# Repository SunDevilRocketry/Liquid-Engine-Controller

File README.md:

<h1>Liquids Engine Controller</h1>

<p>Current PCB Revision: 5.1</p>
<p>PCB Part Number: L0002</p>

<p>The Liquid Engine Controller is the main embedded processor of Sun Devil Rocketry's Liquid Engine. As the brains of the engine, the controller is responsible for executing propellant feed sequences semi-autonomously, logging sensor data, and transmitting engine telemetry. The controller is equipped with an STM32 ARM Cortex M7 processor and 4Mb of external flash for data logging. The board includes a micro-SD card jack for easy access to the logged data. The board includes many power sources for flexible use of the controller during testing and normal operation. These include a 12V power jack, a USB Type B connector, and a 2-pin male pin header. The board includes short circuit protection on the main power rail and regulates the multiplexed supply to 5V and 3.3V with a buck converter and linear regulator (LDO) respectively. The board interfaces with a PC through either the USB port or the 8-pin telemetry connector, which allows wireless transceiver modules with either a UART or SPI interface to be connected. The screw terminals on the board connect to the ignition circuitry. An e-match is used to initiate combustion, and two continuity wires are used to provide the controller feedback on the ignition state. The ignition current is routed through an additional screw terminal which serves as a safety/arming switch. The board interfaces with all of the engine sensors, including eight pressure transducers, a thermocouple, and a load cell. The pressure transducer outputs are amplified with a programmable-gain instrumentation amplifier, which allows for up to 256 calibration settings. The thermocouple output is processed using a cold-junction compensation IC. Additionally, the board includes a reset button and several LEDs for visual indication of power and firmware status.
</p>

<p><b>Working Directory Structure:</b></p>

<p>
   cad: 3d models

   doc: documentation

   img: images of circuit/footprints for github display 
   
   lib: libraries for schematic symbols and footprints

   production: files needed for pcb fabrication, e.g. gerbers, profile, drill file

   sim: simulation models/files 

   src: source design files, e.g. schematic and PCB layout files
</p>

<h2>3D Model: </h2>

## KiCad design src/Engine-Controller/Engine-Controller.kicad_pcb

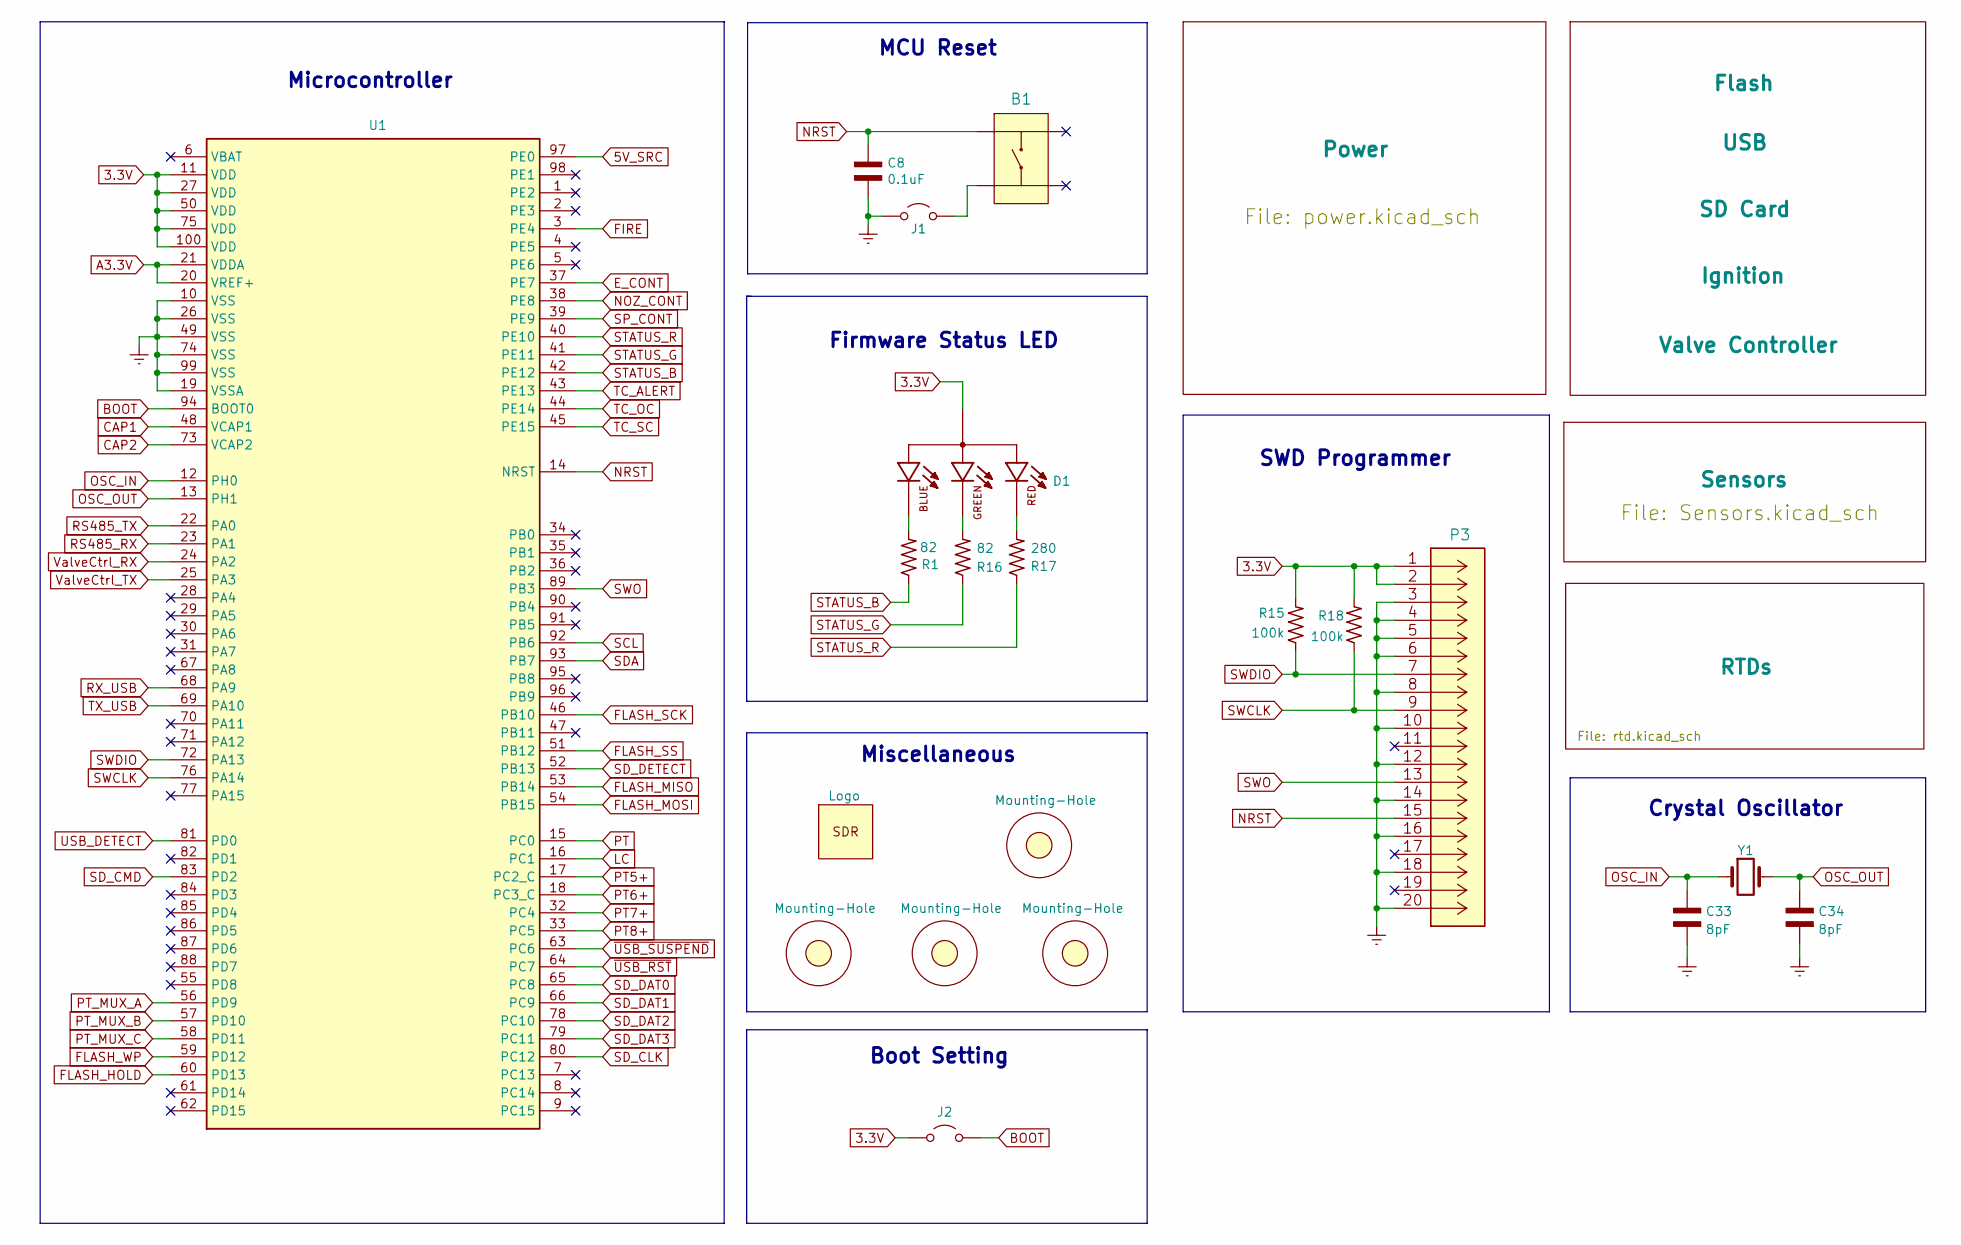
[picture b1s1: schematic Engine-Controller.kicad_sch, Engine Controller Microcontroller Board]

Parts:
B1: PTS647SM38SMTR2LFS
C8: 0.1uF; CAP_0603
C33, C34: 8pF; CAP_0603
D1: CLMVC-FKA-CL1D1L71BB7C3C3
H1, H4, H5, H6: Mounting-Hole; MountingHole_4.3mm_M4_DIN965
J1, J2: Jumper_NO; Jumper-NO
LOGO2: Logo
P3: 3220-20-0200-00
R1, R16: 82; RES_0603
R15, R18: 100k; RES_0603
R17: 280; RES_0603
U1: STM32H750VBTx; STM32H750VBT6
Y1: ECS-240-18-33-JGN-TR

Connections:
3.3V: D1.1, J2.1 (A), P3.1, P3.2, R15.2, R18.2, U1.11 (VDD), U1.27 (VDD), U1.50 (VDD), U1.75 (VDD), U1.100 (VDD); also elsewhere on the board
5V_SRC: U1.97 (PE0); also elsewhere on the board
A3.3V: U1.20 (VREF+), U1.21 (VDDA); also elsewhere on the board
BOOT: J2.2 (B), U1.94 (BOOT0)
CAP1: U1.48 (VCAP1); also elsewhere on the board
CAP2: U1.73 (VCAP2); also elsewhere on the board
E_CONT: U1.37 (PE7); also elsewhere on the board
Earth: C8.1, C33.2, C34.2, J1.1 (A), P3.3, P3.4, P3.5, P3.6, P3.8, P3.10, P3.12, P3.14, P3.16, P3.18, P3.20, U1.10 (VSS), U1.19 (VSSA), U1.26 (VSS), U1.49 (VSS), U1.74 (VSS), U1.99 (VSS); also elsewhere on the board
FIRE: U1.3 (PE4); also elsewhere on the board
FLASH_HOLD: U1.60 (PD13); also elsewhere on the board
FLASH_MISO: U1.53 (PB14); also elsewhere on the board
FLASH_MOSI: U1.54 (PB15); also elsewhere on the board
FLASH_SCK: U1.46 (PB10); also elsewhere on the board
FLASH_SS: U1.51 (PB12); also elsewhere on the board
FLASH_WP: U1.59 (PD12); also elsewhere on the board
LC: U1.16 (PC1); also elsewhere on the board
NOZ_CONT: U1.38 (PE8); also elsewhere on the board
NRST: B1.3, C8.2, P3.15, U1.14 (NRST)
unnamed: D1.2, R1.2
unnamed: D1.3, R16.2
unnamed: D1.4, R17.2
unnamed: B1.1, J1.2 (B)
OSC_IN: C33.1, U1.12 (PH0), Y1.1
OSC_OUT: C34.1, U1.13 (PH1), Y1.3
PT: U1.15 (PC0); also elsewhere on the board
PT5+: U1.17 (PC2_C); also elsewhere on the board
PT6+: U1.18 (PC3_C); also elsewhere on the board
PT7+: U1.32 (PC4); also elsewhere on the board
PT8+: U1.33 (PC5); also elsewhere on the board
PT_MUX_A: U1.56 (PD9); also elsewhere on the board
PT_MUX_B: U1.57 (PD10); also elsewhere on the board
PT_MUX_C: U1.58 (PD11); also elsewhere on the board
RS485_RX: U1.23 (PA1); also elsewhere on the board
RS485_TX: U1.22 (PA0); also elsewhere on the board
RX_USB: U1.68 (PA9); also elsewhere on the board
SCL: U1.92 (PB6); also elsewhere on the board
SDA: U1.93 (PB7); also elsewhere on the board
SD_CLK: U1.80 (PC12); also elsewhere on the board
SD_CMD: U1.83 (PD2); also elsewhere on the board
SD_DAT0: U1.65 (PC8); also elsewhere on the board
SD_DAT1: U1.66 (PC9); also elsewhere on the board
SD_DAT2: U1.78 (PC10); also elsewhere on the board
SD_DAT3: U1.79 (PC11); also elsewhere on the board
SD_DETECT: U1.52 (PB13); also elsewhere on the board
SP_CONT: U1.39 (PE9); also elsewhere on the board
STATUS_B: R1.1, U1.42 (PE12)
STATUS_G: R16.1, U1.41 (PE11)
STATUS_R: R17.1, U1.40 (PE10)
SWCLK: P3.9, R18.1, U1.76 (PA14)
SWDIO: P3.7, R15.1, U1.72 (PA13)
SWO: P3.13, U1.89 (PB3)
TC_ALERT: U1.43 (PE13); also elsewhere on the board
TC_OC: U1.44 (PE14); also elsewhere on the board
TC_SC: U1.45 (PE15); also elsewhere on the board
TX_USB: U1.69 (PA10); also elsewhere on the board
USB_DETECT: U1.81 (PD0); also elsewhere on the board
ValveCtrl_RX: U1.24 (PA2); also elsewhere on the board
ValveCtrl_TX: U1.25 (PA3); also elsewhere on the board
~USB_RST: U1.64 (PC7); also elsewhere on the board
~USB_SUSPEND: U1.63 (PC6); also elsewhere on the board

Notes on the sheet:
SWD Programmer
Miscellaneous
Crystal Oscillator
Microcontroller
Boot Setting
Firmware Status LED
MCU Reset

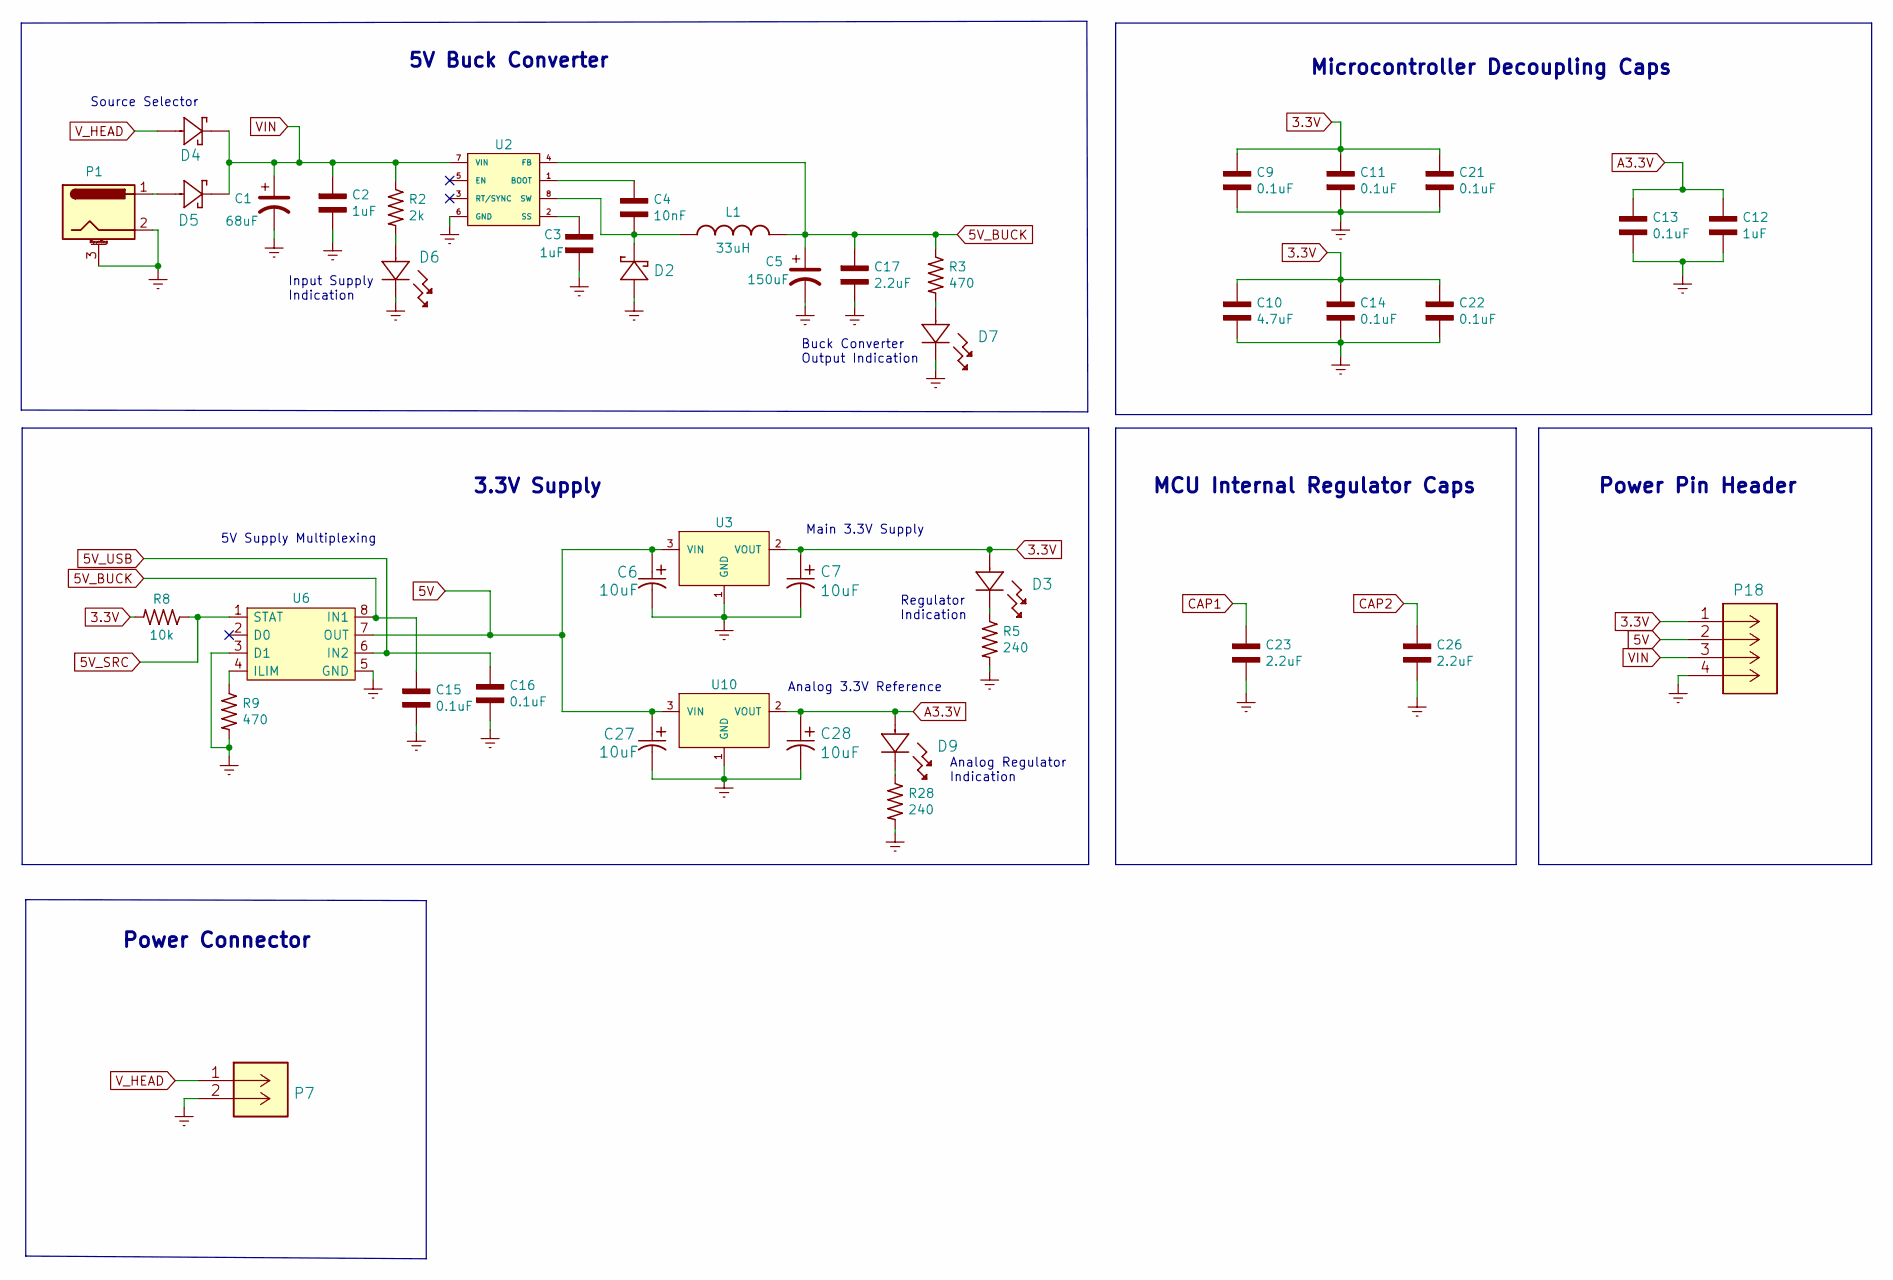
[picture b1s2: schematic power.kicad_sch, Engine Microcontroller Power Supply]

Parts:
C1: 68uF; EEEFPV680XAP
C2, C3, C12: 1uF; CAP_0603
C4: 10nF; CAP_0603
C5: 150uF; EEEFP1E151AL
C6, C7, C27, C28: 10uF; T491A106K010AT
C9, C11, C13, C14, C15, C16, C21, C22: 0.1uF; CAP_0603
C10: 4.7uF; CAP_0603
C17, C23, C26: 2.2uF; CAP_0603
D2: RB160VAM-60TR
D3, D6, D7, D9: SML-LX1206GC-TR
D4, D5: SM5819PL-TP
L1: 33uH; SRP1038A-330M
P1: EJ508A; 12V_power_jack
P7: 647676-2
P18: PPTC041LFBN-RC
R2: 2k; RES_0603
R3, R9: 470; RES_0603
R5, R28: 240; RES_0603
R8: 10k; RES_0603
U2: LM22672MRE-5.0_NOPB
U3, U10: LMS8117AMP-3.3_NOPB; LMS8117AMP-3.3NOPB
U6: TPS2115APWR

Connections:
3.3V: C7.1, C9.2, C10.2, C11.2, C14.2, C21.2, C22.2, D3.2, P18.1 (+12V), R8.2, U3.2 (VOUT); also elsewhere on the board
5V: C6.1, C27.1, P18.2 (GND), U3.3 (VIN), U6.7 (OUT), U10.3 (VIN); also elsewhere on the board
5V_BUCK: C5.1, C15.2, C17.2, L1.2, R3.1, U2.4 (FB), U6.8 (IN1)
5V_SRC: R8.1, U6.1 (STAT); also elsewhere on the board
5V_USB: C16.2, U6.6 (IN2); also elsewhere on the board
A3.3V: C12.2, C13.2, C28.1, D9.2, U10.2 (VOUT); also elsewhere on the board
CAP1: C23.2; also elsewhere on the board
CAP2: C26.2; also elsewhere on the board
Earth: C1.2, C2.1, C3.1, C5.2, C6.2, C7.2, C9.1, C10.1, C11.1, C12.1, C13.1, C14.1, C15.1, C16.1, C17.1, C21.1, C22.1, C23.1, C26.1, C27.2, C28.2, D2.2, D6.1, D7.1, P1.2, P1.3 (MountPin), P7.2, P18.4, R5.2, R9.2, R28.2, U2.6 (GND), U3.1 (GND), U6.3 (D1), U6.5 (GND), U10.1 (GND); also elsewhere on the board
unnamed: D3.1, R5.1
unnamed: D5.2, P1.1
unnamed: D6.2, R2.2
unnamed: D7.2, R3.2
unnamed: D9.1, R28.1
unnamed: C4.2, U2.1 (BOOT)
unnamed: C3.2, U2.2 (SS)
unnamed: C4.1, D2.1, L1.1, U2.8 (SW)
unnamed: R9.1, U6.4 (ILIM)
VIN: C1.1, C2.2, D4.1, D5.1, P18.3, R2.1, U2.7 (VIN); also elsewhere on the board
V_HEAD: D4.2, P7.1

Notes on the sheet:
Power Connector
Power Pin Header
5V Buck Converter
5V Supply Multiplexing
Main 3.3V Supply
Analog Regulator Indication
Regulator Indication
Buck Converter Output Indication
Microcontroller Decoupling Caps
Input Supply Indication
Analog 3.3V Reference
3.3V Supply
Source Selector
MCU Internal Regulator Caps

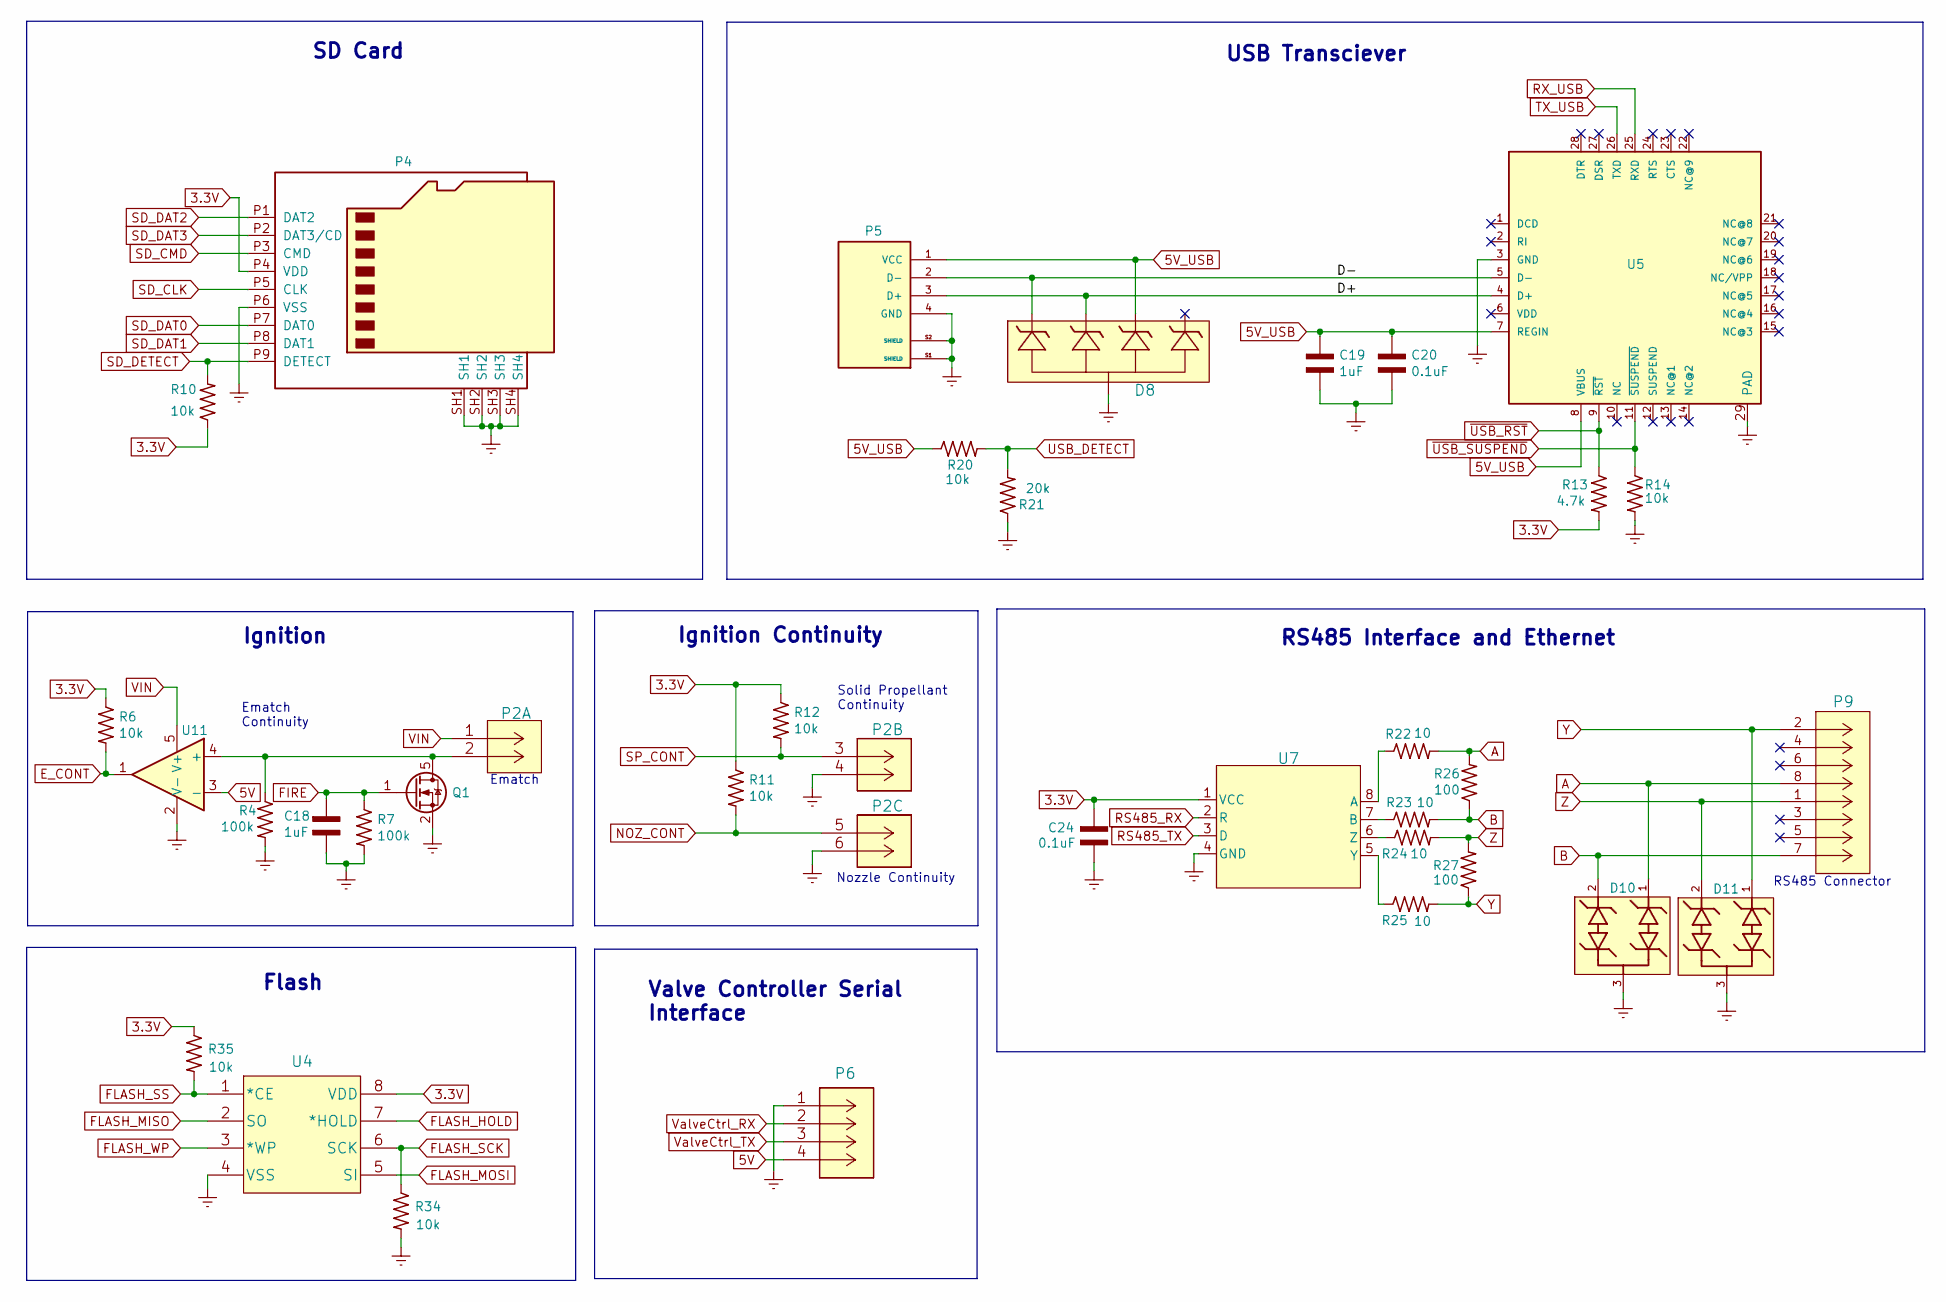
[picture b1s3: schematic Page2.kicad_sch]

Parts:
C18, C19: 1uF; CAP_0603
C20, C24: 0.1uF; CAP_0603
D8: SP0504BAHTG
D10, D11: SMBJ36CA-13-F; CDSOT23-SM712; PARTREV 20-2
P2: 282837-6
P4: Micro_SD_Card; MEM2075-00-140-01-A
P5: USB; USB-TypeB
P6: 140-504-415-000
P9: 54602-908LF
Q1: QS5U17TR
R4, R7: 100k; RES_0603
R6, R10, R11, R12, R14, R20, R34, R35: 10k; RES_0603
R13: 4.7k; RES_0603
R21: 20k; RES_0603
R22, R23, R24, R25: 10; RES_0603
R26, R27: 100; RES_0603
U4: SST25VF040B-50-4I-S2AE-T
U5: CP2102-GMR(QFN28); CP2012-GMR; MPN CP2102-GMR
U7: SN65HVD71DR
U11: TS391IYLT

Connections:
3.3V: C24.2, P4.P4 (VDD), R6.1, R10.1, R11.1, R12.1, R13.2, R35.1, U4.8 (VDD), U7.1 (VCC); also elsewhere on the board
5V: P6.4, U11.3 (-); also elsewhere on the board
5V_USB: C19.2, C20.2, D8.4, P5.1 (VCC), R20.1, U5.7 (REGIN), U5.8 (VBUS); also elsewhere on the board
/Page2/D+: D8.3, P5.3 (D+), U5.4 (D+)
/Page2/D-: D8.1, P5.2 (D-), U5.5 (D-)
A: D10.1, P9.8, R22.2, R26.2
B: D10.2, P9.7, R23.2, R26.1
E_CONT: R6.2, U11.1; also elsewhere on the board
Earth: C18.1, C19.1, C20.1, C24.1, D8.2, D10.3, D11.3, P2.4 (6), P2.6, P4.P6 (VSS), P4.SH1, P4.SH2, P4.SH3, P4.SH4, P5.4 (GND), P5.S1 (SHIELD), P5.S2 (SHIELD), P6.1 (+12V), Q1.2 (S), R4.2, R7.2, R14.2, R21.1, R34.2, U4.4 (VSS), U5.3 (GND), U5.29 (PAD), U7.4 (GND), U11.2 (V-); also elsewhere on the board
FIRE: C18.2, Q1.1 (G), R7.1; also elsewhere on the board
FLASH_HOLD: U4.7 (*HOLD); also elsewhere on the board
FLASH_MISO: U4.2 (SO); also elsewhere on the board
FLASH_MOSI: U4.5 (SI); also elsewhere on the board
FLASH_SCK: R34.1, U4.6 (SCK); also elsewhere on the board
FLASH_SS: R35.2, U4.1 (*CE); also elsewhere on the board
FLASH_WP: U4.3 (*WP); also elsewhere on the board
NOZ_CONT: P2.5, R11.2; also elsewhere on the board
unnamed: P2.2 (6), Q1.5 (D), R4.1, U11.4 (+)
unnamed: R22.1, U7.8 (A)
unnamed: R23.1, U7.7 (B)
unnamed: R25.1, U7.5 (Y)
unnamed: R24.1, U7.6 (Z)
RS485_RX: U7.2 (R); also elsewhere on the board
RS485_TX: U7.3 (D); also elsewhere on the board
RX_USB: U5.25 (RXD); also elsewhere on the board
SD_CLK: P4.P5 (CLK); also elsewhere on the board
SD_CMD: P4.P3 (CMD); also elsewhere on the board
SD_DAT0: P4.P7 (DAT0); also elsewhere on the board
SD_DAT1: P4.P8 (DAT1); also elsewhere on the board
SD_DAT2: P4.P1 (DAT2); also elsewhere on the board
SD_DAT3: P4.P2 (DAT3/CD); also elsewhere on the board
SD_DETECT: P4.P9 (DETECT), R10.2; also elsewhere on the board
SP_CONT: P2.3 (5), R12.2; also elsewhere on the board
TX_USB: U5.26 (TXD); also elsewhere on the board
USB_DETECT: R20.2, R21.2; also elsewhere on the board
VIN: P2.1 (5), U11.5 (V+); also elsewhere on the board
ValveCtrl_RX: P6.2 (GND); also elsewhere on the board
ValveCtrl_TX: P6.3; also elsewhere on the board
Y: D11.1, P9.2, R25.2, R27.1
Z: D11.2, P9.1, R24.2, R27.2
~USB_RST: R13.1, U5.9 (~RST); also elsewhere on the board
~USB_SUSPEND: R14.1, U5.11 (~SUSPEND); also elsewhere on the board

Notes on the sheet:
SD Card
RS485 Connector
Ematch
RS485 Interface and Ethernet
USB Transciever
Ignition Continuity
Ematch Continuity
Ignition
Flash
Nozzle Continuity
Solid Propellant Continuity
Valve Controller Serial Interface

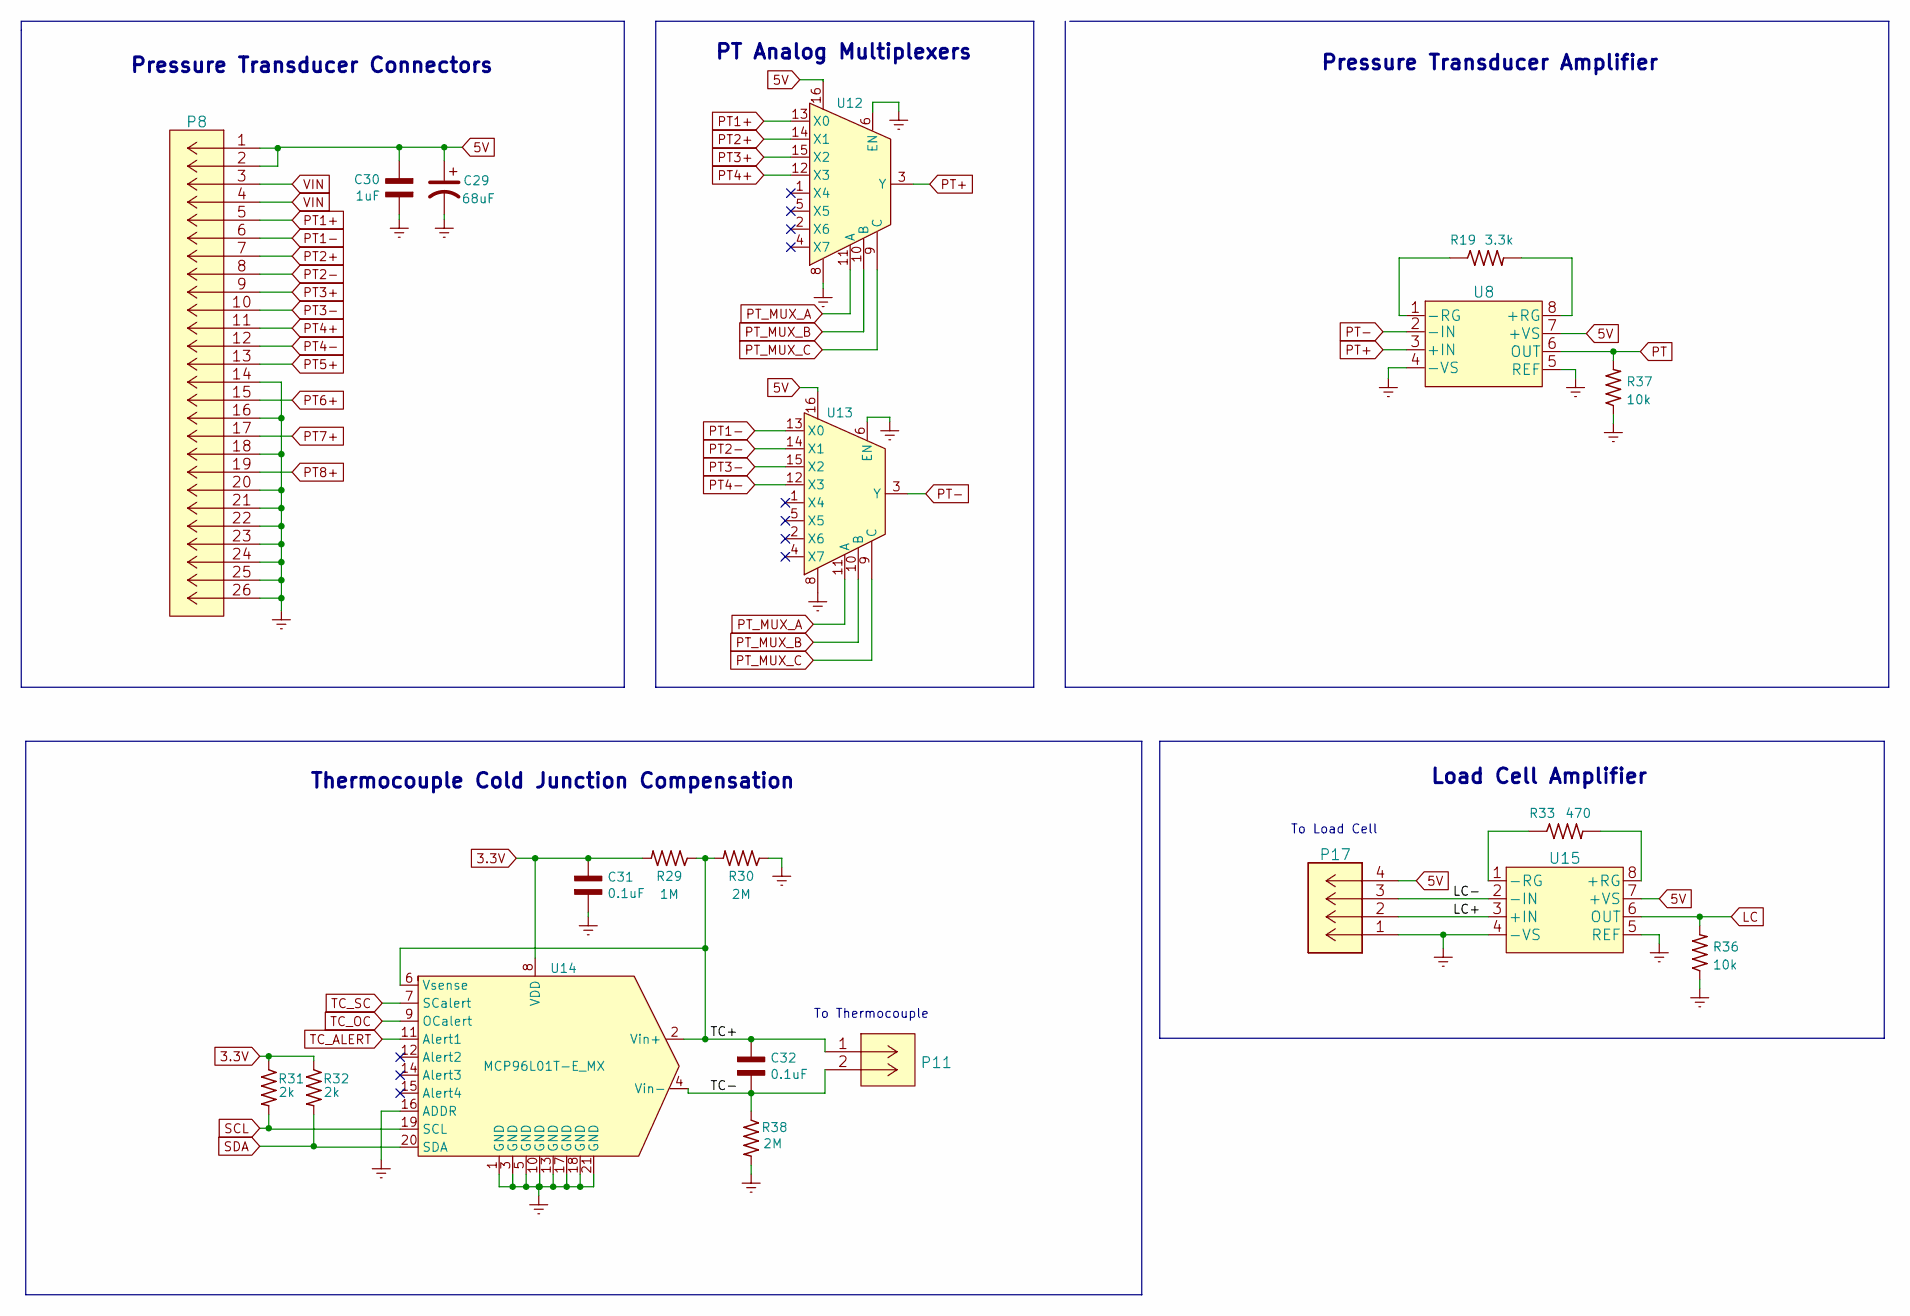
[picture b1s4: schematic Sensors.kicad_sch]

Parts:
C29: 68uF; EEEFPV680XAP
C30: 1uF; CAP_0603
C31, C32: 0.1uF; CAP_0603
P8: 20021511-00026T4LF
P11: 282837-2
P17: 0530470410
R19: 3.3k; RES_0805
R29: 1M; RES_0603
R30, R38: 2M; RES_0603
R31, R32: 2k; RES_0603
R33: 470; RES_0805
R36, R37: 10k; RES_0603
U8, U15: AD623ARZ-R7
U12, U13: MAX4617EUE+T; max4617eue
U14: MCP96L01T-E_MX

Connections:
3.3V: C31.2, R29.2, R31.1, R32.1, U14.8 (VDD); also elsewhere on the board
5V: C29.1, C30.2, P8.1, P8.2, P17.4, U8.7 (+VS), U12.16, U13.16, U15.7 (+VS); also elsewhere on the board
/Sensors/LC+: P17.2 (GND), U15.3 (+IN)
/Sensors/LC-: P17.3, U15.2 (-IN)
/Sensors/TC+: C32.2, P11.1 (5), R29.1, R30.2, U14.2 (Vin+), U14.6 (Vsense)
/Sensors/TC-: C32.1, P11.2 (6), R38.1, U14.4 (Vin-)
Earth: C29.2, C30.1, C31.1, P8.14, P8.16, P8.18, P8.20, P8.21, P8.22, P8.23, P8.24, P8.25, P8.26, P17.1 (+12V), R30.1, R36.1, R37.1, R38.2, U8.4 (-VS), U8.5 (REF), U12.6 (EN), U12.8, U13.6 (EN), U13.8, U14.1 (GND), U14.3 (GND), U14.5 (GND), U14.10 (GND), U14.13 (GND), U14.16 (ADDR), U14.17 (GND), U14.18 (GND), U14.21 (GND), U15.4 (-VS), U15.5 (REF); also elsewhere on the board
LC: R36.2, U15.6 (OUT); also elsewhere on the board
unnamed: R19.2, U8.8 (+RG)
unnamed: R19.1, U8.1 (-RG)
unnamed: R33.2, U15.8 (+RG)
unnamed: R33.1, U15.1 (-RG)
PT: R37.2, U8.6 (OUT); also elsewhere on the board
PT1+: P8.5, U12.13 (X0)
PT1-: P8.6, U13.13 (X0)
PT2+: P8.7, U12.14 (X1)
PT2-: P8.8, U13.14 (X1)
PT3+: P8.9, U12.15 (X2)
PT3-: P8.10, U13.15 (X2)
PT4+: P8.11, U12.12 (X3)
PT4-: P8.12, U13.12 (X3)
PT5+: P8.13; also elsewhere on the board
PT6+: P8.15; also elsewhere on the board
PT7+: P8.17; also elsewhere on the board
PT8+: P8.19; also elsewhere on the board
PT+: U8.3 (+IN), U12.3 (Y)
PT-: U8.2 (-IN), U13.3 (Y)
PT_MUX_A: U12.11 (A), U13.11 (A); also elsewhere on the board
PT_MUX_B: U12.10 (B), U13.10 (B); also elsewhere on the board
PT_MUX_C: U12.9 (C), U13.9 (C); also elsewhere on the board
SCL: R31.2, U14.19 (SCL); also elsewhere on the board
SDA: R32.2, U14.20 (SDA); also elsewhere on the board
TC_ALERT: U14.11 (Alert1); also elsewhere on the board
TC_OC: U14.9 (OCalert); also elsewhere on the board
TC_SC: U14.7 (SCalert); also elsewhere on the board
VIN: P8.3, P8.4; also elsewhere on the board

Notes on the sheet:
To Thermocouple
Pressure Transducer Connectors
PT Analog Multiplexers
To Load Cell
Thermocouple Cold Junction Compensation
Pressure Transducer Amplifier
Load Cell Amplifier

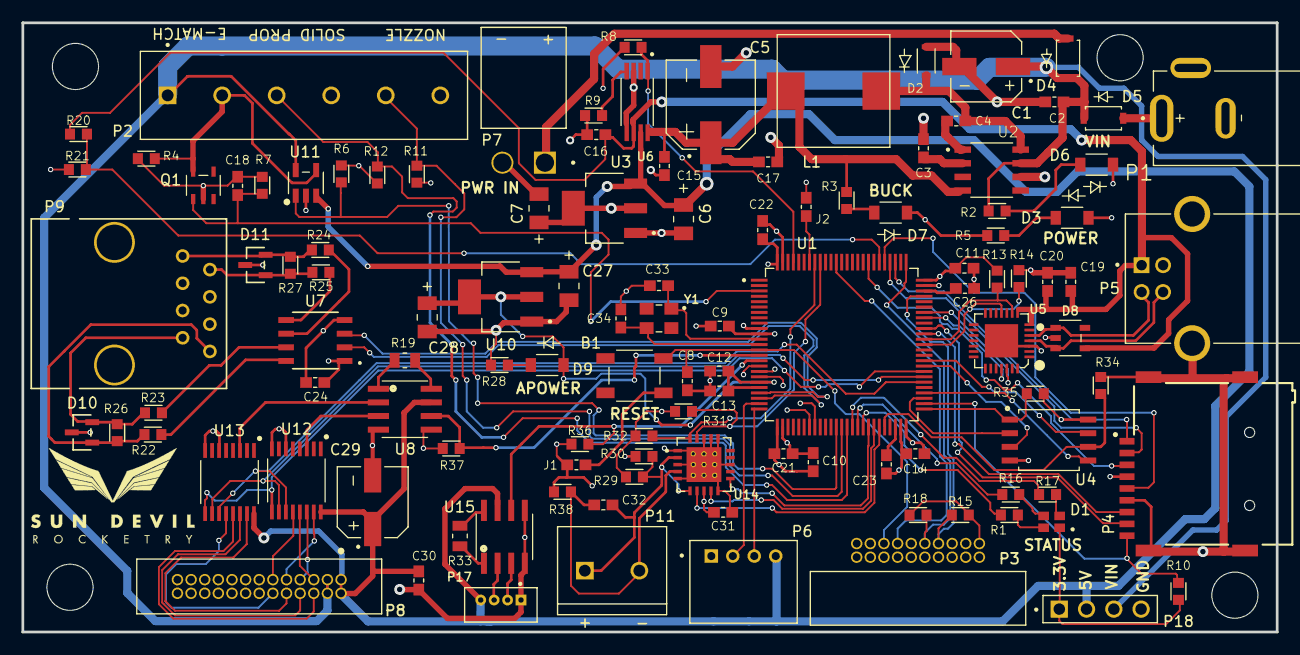
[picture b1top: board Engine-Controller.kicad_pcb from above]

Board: 4 copper layers, 116.8 x 56.7 mm, 119 parts (0 on the bottom side), 103 nets.

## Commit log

2021-06-23 Updated initial README
2021-06-23 Built directory structure
2021-06-23 Added footprints and symbols for microcontroller, LED and resistor
2021-06-26 Added library files for 5V buck converter
2021-06-26 Added library files for switching capacitors
2021-06-26 Added library files for switching output
2021-06-26 Added switching inductor to library files
2021-06-26 Added schottky diode to libraries
2021-06-26 Added switching power supply resistors to library files
2021-06-26 Added library files for 3.3 V regulator
2021-06-26 Added Tantalum Cap to library files
2021-06-26 Added USB connector to library files
2021-06-26 Added step file for USB type B connector
2021-06-26 Started Schematic
2021-06-26 Added subsheet for power supply
2021-06-27 Added programming connector to library files
2021-06-27 Added pin headers to library files
2021-06-27 Added 3D file for pin header
2021-06-27 Added missing pins to microcontroller schematic symbol
2021-06-27 Added testpoints to library files
2021-06-27 Added Polarity indicators to LED and diode footprints
2021-06-27 Updated README with directory structure
2021-06-27 Updated README directory notes
2021-06-30 Updated pinout of Serial connector
2021-06-30 Completed power supply part of schematic
2021-06-30 Annotated Schematic
2021-06-30 Associated Schematic Symbols with footprints
2021-06-30 Resolved all ERC issues
2021-06-30 Added capacitor bypassing RST to ground
2021-07-01 Added test points
2021-07-01 Imported footprints into layout file
2021-07-03 Updated Connector pinouts and added button to Reset pin
2021-07-03 Added buffer to some IOs
2021-07-03 Added NO Jumper to NRST button
2021-07-03 Fixed J1 orientation
2021-07-04 Added Flash
2021-07-04 Added Micro SD Card
2021-07-04 Grounded USB shield
2021-07-04 Moved Programmer to connectors sheet
2021-07-04 Added ADC Inputs
2021-07-04 Added Digital Signals for Flash
2021-07-04 Fixed Schematic ERC erros
2021-07-05 Routed decoupling caps
2021-07-05 Moved 3.3V regulator
2021-07-06 Began connector routing
2021-07-06 Finished connector routing
2021-07-06 Resolved DRC issues
2021-07-06 Generated STEP File
2021-07-06 Added in Micro 3D model to step file
2021-07-10 Added source selector schottky to lib files
2021-07-10 Added voltage source selector to schematic
2021-07-10 Updated buck converter schottky symbol
2021-07-10 Grounded 12V barrel plug detect pin to GND
2021-07-11 Started py script to calculate buck converter external component values
2021-07-11 Added testscript to .gitignore
2021-07-11 Updated .gitignore
2021-07-11 Saved changed
2021-07-13 Added power multiplexor to lib files
2021-07-13 Wired 5V power multiplexor
2021-07-13 Annotated 5V selector parts
2021-07-13 Connected symbols to footprints
2021-07-13 Added new components to PCB
2021-07-20 Changed C1 cap
2021-07-20 Added new C1 cap to PCB layout
2021-07-20 Added ripple current calcs
2021-07-24 Updated L1 inductor
2021-07-24 Removed SWD 3.3V connections
2021-07-24 Finished Routing Rev 2 changes
2021-07-24 Added silkscreen header labels and SDR Logo
2021-07-24 Added info and images to README
2021-07-24 Fixed issue with PCB images
2021-07-25 Generated gerber files
2021-09-22 Changed MCU from M4 to M7
2021-09-22 Added polarity marking to C1
2021-09-22 Removed resistor divider from buck converter
2021-09-22 Added LEDs to all power rails
2021-09-22 changed labels in schematic
2021-09-22 Routed edits to power supply
2021-09-22 Routed GPIO headers
2021-09-22 Routed ADC Headers
2021-09-22 Routed Flash
2021-09-22 Placed New test points
2021-09-22 Re-added SDR Logo
2021-09-28 Added earth symbol to component symbol lib
2021-10-04 Added FTDI chip to lib files
2021-11-07 Added Ignition System to lib and schematic
2021-11-07 Add Internal regulator stability caps
2021-11-08 Updated Buffer Symbol
2021-11-10 Added logo and mounting hole to lib and schematic
2021-11-14 finished routing rev3.0
2021-12-13 Finalized Rev 3.0 Layout
2022-01-03 fixed colors on connectors
2022-01-06 Updated README description
2022-01-06 Updated MCU schematic
2022-01-06 Updated power schematic on README
2022-01-06 Updated README connectors schematic
2022-01-06 Updated README USB schematic
2022-01-06 Added Igntion system to README
2022-01-06 Added 3D veiwer images
2022-01-06 Moved 3D veiwer images to top of README
2022-01-06 Changed PCB header in README
2022-01-28 Added minor changes
2022-02-06 added rgb led, and deleted old status led
2022-02-06 added box around rgb area
2022-02-18 edited rgb led, annotated schematic
2022-03-02 Fixed README typos
2022-03-02 Added line on UART to USB converter to readme
2022-03-06 removed NRST pull up resistor
2022-03-06 updated symbol library
2022-03-06 Cleaned up power schematic
2022-03-06 cleaned up MCU schematic sheet
2022-03-06 updated pcb revision on readme
2022-03-06 Removed misc elements from connectors sheet
2022-03-07 adjusted power supply ceramic capacitances
2022-03-07 merged all non power components into single sheet
2022-03-07 added new sheet for sensor interfaces
2022-03-07 updated SWD connector
2022-03-07 Added connectors for valve controller and main power line
2022-03-07 plotted schematic to pdf
2022-03-08 Added pull up resistors to SWD signals
2022-03-09 updated test points and USB resistors
2022-03-09 minor schematic changes
2022-03-11 added amplifier to lib files
2022-03-11 added multiplexor and analog switch to lib files
2022-03-18 added lib files for pt connectors
2022-03-18 added pt connectors to schematic
2022-03-18 added pt multiplexors to schematic
2022-03-18 added decoder to lib symbols
2022-03-18 added decoder footprint to lib files
2022-03-18 finished pt schematic
2022-03-19 moved schematic components to 25 mil grid
2022-04-18 removed jumper from reset button
2022-04-27 added comparator to lib files
2022-04-27 added comparator to symbol library
2022-04-27 corrected comparator symbol pin numbers
2022-04-27 added comparator to rev 4.0 schematic
2022-04-27 fixed pinout of MOSFET symbol
2022-04-27 added thermocouple IC to lib files
2022-04-27 added thermocouple IC to schematic
2022-04-27 added I2C pullups to thermocouple IC
2022-04-27 added thermocouple sigs to MCU
2022-04-27 added schematic annotations
2022-05-11 added load cell amplifier to schematic
2022-05-11 added power pin header to schematic
2022-05-11 added label to load cell connector
2022-05-11 changed pts to a single connector
2022-05-11 added pull up resistor to flash SS pin
2022-05-12 added crystal oscillator to lib files
2022-05-12 changed crystal oscillator
2022-05-12 added crystal oscillator to schematic
2022-05-12 changed USB/SDcard outlines
2022-05-13 added connector for wireless interface
2022-05-13 added wireless interface to schematic
2022-05-13 fixed border of usb scheamtic section
2022-05-13 resolved all ERC schematic issues
2022-05-13 added rev 4 schematic images to readme
2022-05-13 widened MCU schematic image
2022-05-13 removed unused traces in layout
2022-05-13 added safety switch screw terminal to lib files
2022-05-13 added safety switch to schematic
2022-05-14 removed pt connector part no. from footprint
2022-05-14 removed uncessary caps from MCU LDO pins
2022-05-14 removed uneccessary info from footprint lib files
2022-05-14 added load resistors to amplifier outputs
2022-05-15 routed rev4
2022-05-15 resolved minor DRC errors
2022-05-16 changed TC connector to be different from power connector
2022-05-16 fixed spelling errors in readme description
2022-05-22 minor lib file changes
2022-05-22 moved uart chip decoupling capacitors closer to IC pins
2022-05-28 generated production files
2022-05-29 Added initial PT gain calc code
2022-06-10 Added in the plotting function
2022-06-10 minor changes
2022-06-19 Added user input error code, output in convenient unit
2022-06-19 deleted backups file
2022-06-19 Float numbers
2022-06-19 Added Comments
2022-06-26 minor local changes
2022-07-02 renamed 0603 capacitor step file to CAP_0603.step
2022-07-07 local changes to binary files
2023-04-04 created rev5 schematic, added USB detection, updated PT readout circuits
2023-04-04 completed rev 5.0 layout
2023-06-08 removed wireless interface connector
2023-06-08 added RS485 interface parts to lib files
2023-06-08 implemented RS485 interface
2023-06-08 fixed valve controller connector by reversing connections
2023-06-08 added RS485 RX/TX signals to MCU
2023-06-09 changed blue LED from 62 ohm to 82 ohm to match green led resistor
2023-06-09 plotted schematic
2023-06-09 fixed broken paths to step files and placed all 5.1 components on board
2023-06-09 completed initial 5.1 layout
2023-06-09 resolved all DRC errors
2023-06-09 added readme images, exported 5.1 3D model and schematic
2023-06-09 copied over 5.0/5.1 updates from Gain-Calc branch
2023-06-09 re-added deleted legacy parts to lib files
2023-06-09 added legacy parts from Rev 2.0 to lib files

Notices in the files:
parts and their libraries:
Copyright 2021 Accelerated Designs. All rights reserved.
